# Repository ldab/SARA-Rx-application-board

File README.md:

# SARA-Rx application board

 SARA-R4 NB-IoT + Cat-M1 + GNSS application board - NINA-B3 with Secure MQTT

# **:heavy_exclamation_mark:BEFORE YOU DO ANYTHING, CHECK BATTERY POLARITY:heavy_exclamation_mark:**

## TODO

- [ ] More details about battery etc...
- [ ] !!! Better Socket close URC handler.
- [ ] Check AT response based on the last chars, in order to avoid missing URCs when after "OK" for example
- [ ] Implement Subscribe;

## Energy Budget

* 88mA active current;
* Code takes ~10 seconds to execute;
* Wakes every hour;
* 40uA Sleep current;
* 10 hours of light available;
* V charge ready = 3.67V;
* V Over discharge = 3.6V;
* V Over charge = 4.12V;

**Source Power Required = 3.8mW**

**Storage Required = 4.73mAh**

### Sleep Current

| Component 	| Current 	|
|-----------	|---------	|
| SARA-R410 	| 7uA     	|
| NINA-B3   	| 3uA     	|
| Batt ADC  	| 3uA     	|
| SHTC3     	| 0.5uA   	|
| TP4054    	| 1uA     	|
| TXS0108   	| 5uA(?)  	|
| TPS61021A  	| 17uA   	  |
| TOTAL     	| ~37uA   	|

## Nordic SDK

* This is based on nRF5_SDK_16.0.0_98a08e2, get yours here: https://www.nordicsemi.com/Software-and-tools/Software/nRF5-SDK/Download

1. Sign in to the AWS IoT Console
2. Register a Device in the Registry
3. Configure Your Device
4. View Device MQTT Messages with the AWS IoT MQTT Client

https://docs.aws.amazon.com/iot/latest/developerguide/iot-gs.html

* 120mA active current;
* Code takes 15 seconds to execute;
* Wakes every hour;
* 2mA Sleep current *This needs to be optimized*;
* 10 hours of light available;
* V charge ready = 3.67V;
* V Over discharge = 3.6V;
* V Over charge = 4.12V;

1. Clone this repo to a local folder ```> git clone https://github.com/ldab/SARA-Rx-application-board```
2. Point the `$(SDK)` @`./code/ninab3/blank/ses/libuarte_pca10056.emProject` to where you have installed Nordic SDK, for example `C:\nRF\nRF5_SDK_16.0.0_98a08e2`
3. Like so: `macros="CMSIS_CONFIG_TOOL=C:/nRF/nRF5_SDK_16.0.0_98a08e2/external_tools/cmsisconfig/CMSIS_Configuration_Wizard.jar;SDK=C:/nRF/nRF5_SDK_16.0.0_98a08e2"`
4. Open the SEGGER Embedded Studio project file located in `./code/ninab3/blank/ses/libuarte_pca10056.emProject`

* PS. don't forget to set the NFC Pins as GPIO on the Preprocessor: `CONFIG_NFCT_PINS_AS_GPIOS`

Ref. https://devzone.nordicsemi.com/f/nordic-q-a/44638/how-to-move-an-sdk-example-out-of-the-sdk-tree

## IoT Dashboard

* Adafruit https://io.adafruit.com provides a free MQTT broker with a Dashboard allowing this project to be displayed publicly with little to no effort
  * Create an account and insert your KEY as the `MQTT_PASS`
  * `MQTT_USER` is the username used for creating the account.

* Adafruit expect data as a json, for example:

    ```
    sprintf(_msg, "{\"feeds\": {\"T\": %.01f,\"H\": %.01f,\"Bpc\": %d,\"RSRP\": %.02f,\"Bv\": %.02f}}",
            temperature, humidity, batt_lvl_in_percentage, modemInfo.RSRP, _b)
    ```

* The topic, groups and feeds are created automagically, on the example the MAC address is added as an identifier:

    ```
    sprintf(topic, "lbispo/g/nina_%X/json", NRF_FICR->DEVICEADDR[0]);
    ```

https://io.adafruit.com/lbispo/dashboards/moree?kiosk=true

## Efficiency

## Schematic

## PCB

## BOM

## Enclosure

## Kown issues, limintations

* MQTT Socket Implementaition can only **publish** QoS 0 messages.

## Thoughts or Improvements

* Use STATUS 2 of AEM10941 as last grasp;
* Control boost converter EN, in order to turn SARA Off;
  * Remove boost converter, as it does not boost a lot since Vbatt ON = 3.6V.
* SARA RESET Pin access;
* Use 101b AEM10941 Configuration in order to Vovdis = 3.0V givin extra ~20% battery (?).
* Open Drain 74LVC3G07 buffer on NINA LED, in order to avoid leakage.

## Credits

* [MQTTBox](http://workswithweb.com/mqttbox.html) for Windows in order to communicate with the broker and check messages;
* [CloudMQTT](https://www.cloudmqtt.com/) Free Cloud Broker;
* MQTT implementation inspired and based on [knolleary PubSub Client](https://github.com/knolleary/pubsubclient);
* AT Commands implementation inspired on [vshymanskyy TinyGSM](https://github.com/vshymanskyy/TinyGSM);
* GitHub Shields and Badges created with [Shields.io](https://github.com/badges/shields/);

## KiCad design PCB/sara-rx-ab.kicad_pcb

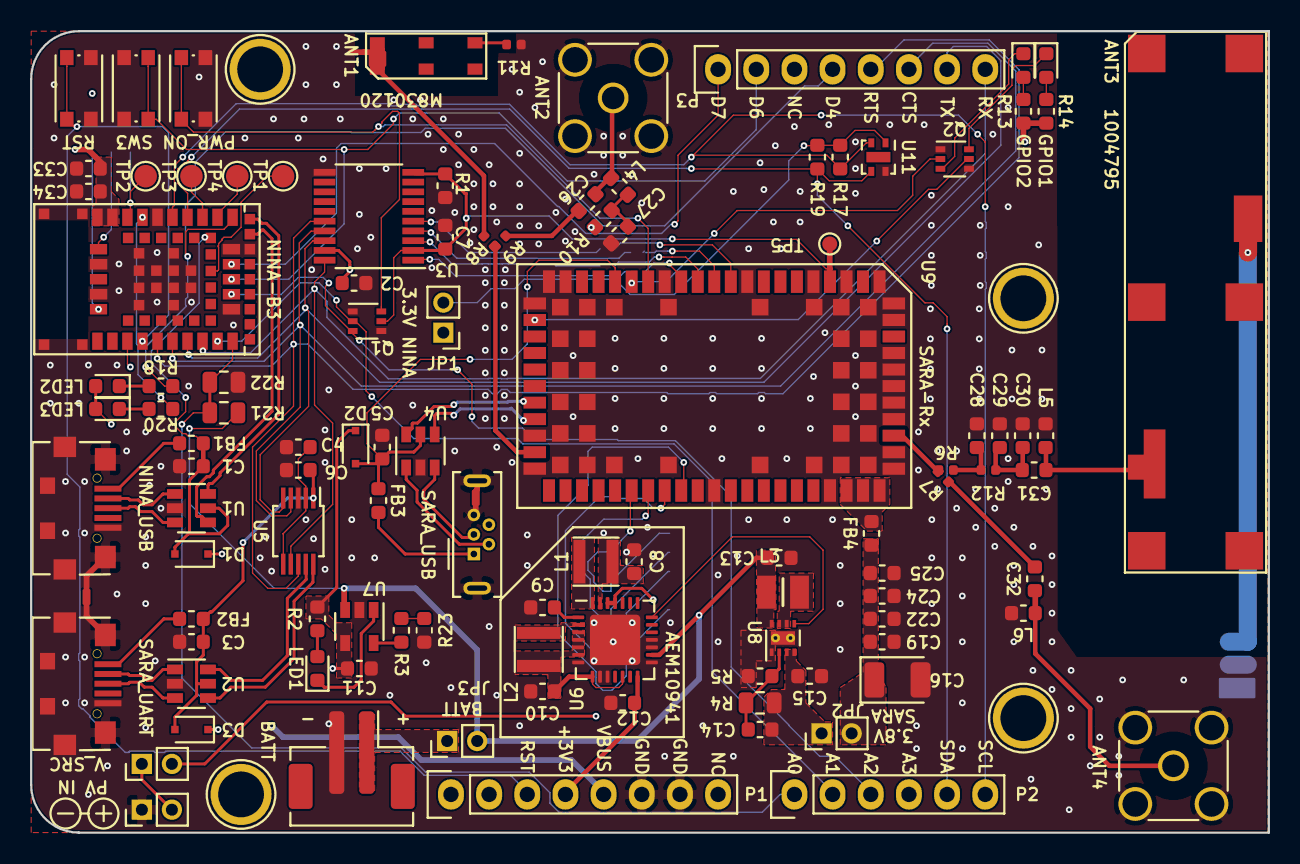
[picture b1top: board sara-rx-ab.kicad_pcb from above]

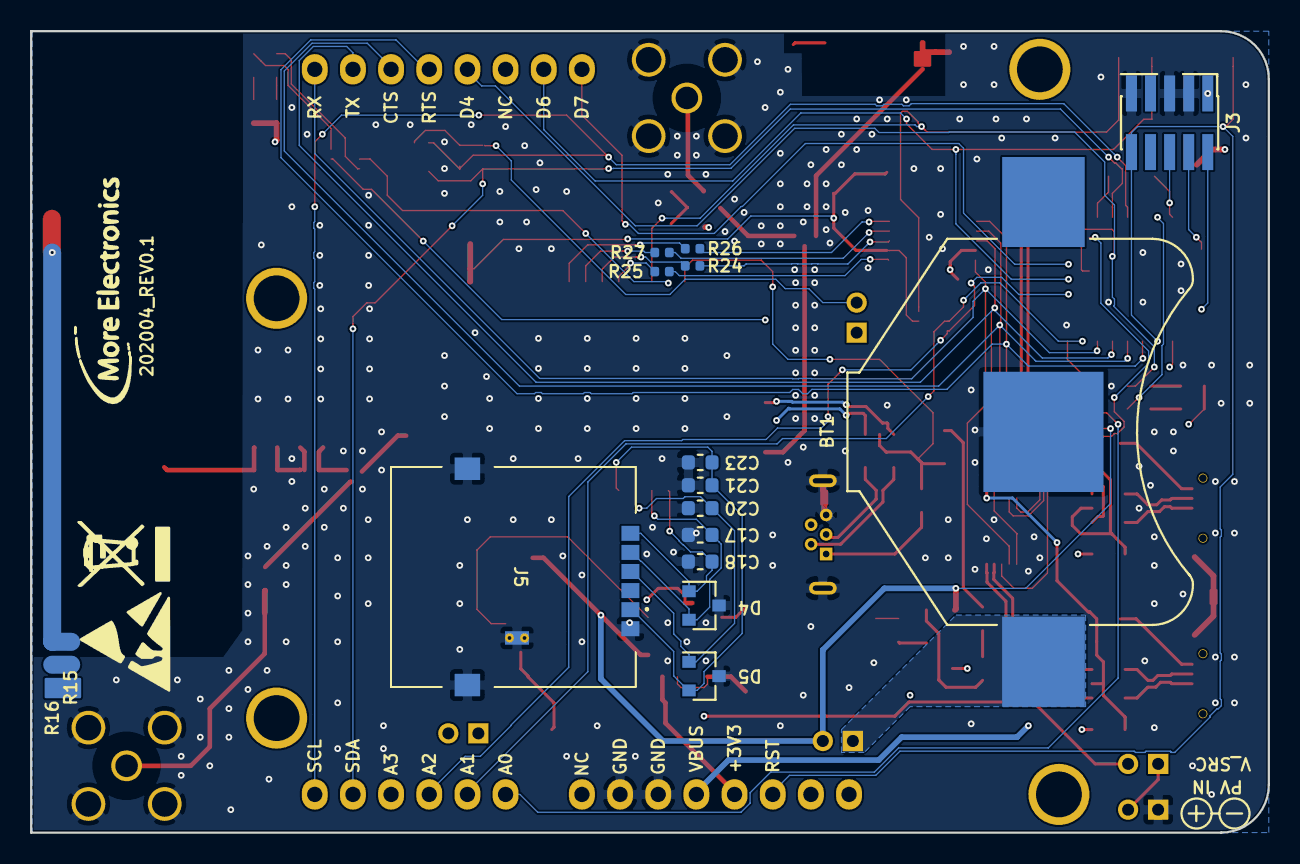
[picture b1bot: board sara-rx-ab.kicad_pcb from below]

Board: 4 copper layers, 82.4 x 53.3 mm, 128 parts (16 on the bottom side), 99 nets.

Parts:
ANT1: M830120
ANT2: Conn_Coaxial; SMA_Amphenol_132291_Vertical
ANT3: PCB ANT 1004795; 1009475
ANT4: EXT Antenna; SMA_Amphenol_132291_Vertical
BT1: LIR2450; BatteryHolder_Keystone_3008_1x2450
BT2: EXT BATT; JST_PH_B2B-PH-SM4-TB_1x02-1MP_P2.00mm_Vertical
C1, C2, C3, C5, C6, C7, C19, C23, C33, C34: 100n; C_0603_1608Metric
C4: 1u; C_0603_1608Metric
C8, C9, C10, C11, C12, C13, C15: 10u; C_0603_1608Metric
C14, C31: 4.7p; C_0603_1608Metric
C16: 100u; CP_EIA-3528-21_Kemet-B
C17, C18, C20, C21, C26: 47p; C_0603_1608Metric
C22, C27: 10n; C_0603_1608Metric
C24, C32: 15p; C_0603_1608Metric
C25: 68p; C_0603_1608Metric
C28: 5p; C_0603_1608Metric
C29: DNP; C_0603_1608Metric
C30: 0.3p; C_0603_1608Metric
D1, D2, D3: PMEG4010CEJ; D_SOD-323F
D4, D5: PESD5V0U2BT; SOT-23
FB1, FB2, FB3, FB4: BLM18EG221SN1D; L_0603_1608Metric
GPIO1, GPIO2: LTST-C191KGKT; LED_0603_1608Metric
J1: SOLAR PV; PinHeader_1x02_P2.00mm_Vertical
J2, J4: Bridge; 4Layer_15mil
J3: FTSH-105-01; SWD_JTAG
J5: SMO-1512; SMO1512
J6: Bridge; 4Layer_square
JP1, JP2, JP3, JP4: Jumper_NC_Small; PinHeader_1x02_P2.00mm_Vertical
L1, L2: 10u; L_Taiyo-Yuden_NRH30xx
L3: DFE252012P-R47M=P2; INDC2520X120N
L4: 27n; L_0603_1608Metric
L5: 8.2n; L_0603_1608Metric
L6: 39n; L_0603_1608Metric
LED1, LED2: 19-217/R6C-AL1M2VY/3T; LED_0603_1608Metric
LED3: LTST-C191KGKT; LED_0603_1608Metric
P1: Power; Socket_Strip_Arduino_1x08
P2: Analog; Socket_Strip_Arduino_1x06
P3: Digital; Socket_Strip_Arduino_1x08
P4, P5, P6, P7: CONN_01X01; Arduino_1pin
Q1, Q2: MUN5214DW1T1G; SOT-363_SC-70-6
R1, R2, R3, R17, R19, R23: 10K; R_0603_1608Metric
R4, R21, R22: 1M±0.1%; R_0805_2012Metric
R5: 267K; R_0603_1608Metric
R6, R8, R11, R12, R15, R16, R24, R25, R26, R27: 0R; R_0402_1005Metric
R7, R9: DNP; R_0402_1005Metric
R10: 10; R_0603_1608Metric
R13, R14, R18, R20: 1K; R_0603_1608Metric
SW1: PWR_ON; SW_Push_1P1T_NO_CK_KMR2
SW2, SW3: KMR2; SW_Push_1P1T_NO_CK_KMR2
TP1, TP2, TP3, TP4: TestPoint; TestPoint_Pad_D1.5mm
TP5: TestPoint; TestPoint_Pad_D1.0mm
U1, U2, U4: USBLC6-2SC6; SOT-23-6
U3: TXS0108EPW; TSSOP-20_4.4x6.5mm_P0.65mm
U5: HT42B534-MSOP; MSOP-10_3x3mm_P0.5mm
U6: AEM10941; QFN-28-1EP_5x5mm_P0.5mm_EP3.35x3.35mm
U7: TP4054; SOT-23-5
U8: TPS61021A; WSON-8-1EP_2x2mm_P0.5mm_EP0.9x1.6mm_ThermalVias
U9: SARA-Rx; ublox_SARA-G3_LGA-96
U10: NINA-B3
U11: SHTC3; AMS_QFN-4-1EP_2x2mm_P0.95mm_EP0.7x1.6mm
USB1: USB_B_Micro; C77238
USB2: USB_B_Micro_C77238; C77238
USB3: USB_B_Micro_C145795; USB_Micro-B_U-D-M5DD-W-1_VERTICAL

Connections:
+1V8: C7.1, Q1.5, R1.2, TP5.1, U3.2, U3.10, U9.4
+3V3: C2.1, C12.1, J3.1, JP1.1, P1.4, U3.19, U6.14
+3V3_NINA: C33.1, C34.1, JP1.2, LED2.2, LED3.2, R17.1, R19.1, U10.9, U10.10, U11.1
+3V8: C14.2, C15.2, JP2.1, R4.2, R10.2, R13.1, R14.1, U8.3, U8.4
+3V8_SARA: C16.1, C19.1, C22.1, C24.1, C25.1, FB4.1, JP2.2
+5C: C1.2, D1.2, FB1.1, U1.5, U10.31
+5F: C5.1, D2.2, FB3.1, U4.5, U9.17
+5P: C3.1, C6.2, D3.2, FB2.1, U2.5, U5.1
+BATT_SYS: C13.2, JP3.2, L3.1, R21.1, U6.16, U7.3, U8.8
+V_PV: JP4.2, U6.25, U6.26
/MCU_D+: U1.4, U10.54
/MCU_D-: U1.6, U10.55
/MCU_I_D+: U1.3, USB1.3
/MCU_I_D-: U1.1, USB1.2
/NINA-B3/LED_G: R20.2, U10.7
/NINA-B3/SWC: J3.4, U10.11
/NINA-B3/SWD: J3.2, U10.15
/POWER MGT/LDO_EN: U6.21, U8.5
/POWER MGT/VBATT: BT1.1, BT2.1, JP3.1
/POWER MGT/VBUCK: C10.1, L2.1, U6.3, U6.4, U6.5, U6.6, U6.8, U6.12
/POWER MGT/V_SRC: J1.2, JP4.1
/SARA-Rx/ANT_EXT: C32.2, R7.2
/SARA-Rx/ANT_INT: C28.2, R6.2, R12.1
/SARA-Rx/GNSS_EXT: C26.2, R9.2
/SARA-Rx/GNSS_INT: ANT1.6, J6.1, R8.2
/SARA-Rx/GPIO1: Q2.2, U9.16
/SARA-Rx/GPIO2: Q2.5, U9.23
/SARA-Rx/PWR_ON: Q1.6, SW1.1, U9.15
/SARA-Rx/SARA_CTS: R27.1, U3.4
/SARA-Rx/SARA_RTS: R26.1, U3.5
/SARA-Rx/SARA_RX: R25.1, U3.1
/SARA-Rx/SARA_TX: R24.1, U3.3
/SARA-Rx/SIM_CLK: C18.1, D4.1, J5.C3, U9.38
/SARA-Rx/SIM_IO: C17.1, D4.2, J5.C7, U9.39
/SARA-Rx/SIM_RST: C20.1, D5.1, J5.C2, U9.40
/SARA-Rx/VSIM: C21.1, C23.1, D5.2, J5.C1, U9.41
/SARA_D+: U4.4, U9.29
/SARA_D-: U4.6, U9.28
/SARA_I_D+: U4.3, USB3.3
/SARA_I_D-: U4.1, USB3.2
/UART_D+: U2.4, U5.10
/UART_D-: U2.6, U5.9
/UART_I_D+: U2.3, USB2.3
/UART_I_D-: U2.1, USB2.2
A0\BATT: P2.1, R21.2, R22.1, U10.25
A1\SARA_ON: P2.2, Q1.2, U10.24
A2\V_INT: P2.3, Q1.3, U10.27
A3: P2.4, U10.18
D4\LED_R: P3.4, R18.2, U10.1
D6\SW: P3.2, SW3.1, U10.28
D7: P3.1, U10.29
D10_CS: TP4.1, U10.2
D11_MOSI: TP3.1, U10.3
D12\MISO\SWO\LED_B: J3.6, TP2.1, U10.8
D13_SCK: TP1.1, U10.45
GND: ANT1.1, ANT2.2, ANT4.2, BT1.2, BT2.2, C1.1, C2.2, C3.2, C4.1, C5.2, C6.1, C7.2, C8.2, C9.1, C10.2, C11.2, C12.2, C13.1, C15.1, C16.2, C17.2, C18.2, C19.2, C20.2, C21.2, C22.2, C23.2, C24.2, C25.2, C27.1, C28.1, C29.2, C30.1, C33.2, C34.2, D4.3, D5.3, J1.1, J2.1, J2.2, J3.3, J3.5, J3.9, J4.1, J4.2, J5.C5, J5.MP1, J5.MP2, J6.2, L5.2, L6.2, P1.6, P1.7, Q1.1, Q1.4, Q2.1, Q2.4, R1.1, R5.1, R11.2, R22.2, R23.2, SW1.2, SW2.1, SW3.2, U1.2, U2.2, U3.11, U4.2, U5.3, U6.7, U6.9, U6.10, U6.15, U6.17, U6.18, U6.29, U7.2, U8.1, U8.9, U9.1, U9.3, U9.5, U9.9, U9.14, U9.20, U9.21, U9.22, U9.30, U9.32, U9.43, U9.50, U9.54, U9.55, U9.57, U9.58, U9.59, U9.60, U9.61, U9.63, U9.64, U9.65, U9.66, U9.67, U9.68, U9.69, U9.70, U9.71, U9.72, U9.73, U9.74, U9.75, U9.76, U9.77, U9.78, U9.79, U9.80, U9.81, U9.82, U9.83, U9.84, U9.85, U9.86, U9.87, U9.88, U9.89, U9.90, U9.91, U9.92, U9.93, U9.94, U9.95, U9.96, U10.6, U10.12, U10.14, U10.26, U10.30, U10.53, U10.56, U10.57, U10.58, U10.59, U10.60, U10.61, U10.62, U10.63, U10.64, U10.65, U10.66, U10.67, U10.68, U10.69, U10.70, U10.71, U11.4, USB1.5, USB1.6, USB1.7, USB1.8, USB1.9, USB1.10, USB2.5, USB2.6, USB2.7, USB2.8, USB2.9, USB2.10, USB3.5, USB3.6, USB3.7
MCU_CTS: P3.6, U3.17, U5.4, U10.21
MCU_RTS: P3.5, U3.16, U5.8, U10.20
MCU_RX: P3.8, U3.20, U5.7, U10.23
MCU_TX: P3.7, U3.18, U5.5, U10.22
NINA_RST: J3.10, P1.3, SW2.2, U10.19
unnamed: ANT1.3, R11.1
unnamed: ANT2.1, C26.1, L4.1
unnamed: ANT3.1, C31.1, L5.1
unnamed: ANT3.5, R15.1
unnamed: ANT4.1, C32.1, L6.1
unnamed: C4.2, U5.2, U5.6
unnamed: C8.1, L1.1, U6.27
unnamed: C9.2, U6.1
unnamed: C14.1, R4.1, R5.2, U8.2
unnamed: C27.2, L4.2, R10.1
unnamed: C29.1, C30.2, C31.2, R12.2
unnamed: FB1.2, USB1.1
unnamed: FB2.2, USB2.1
unnamed: FB3.2, USB3.1
unnamed: FB4.2, U9.51, U9.52, U9.53
unnamed: GPIO1.1, Q2.6
unnamed: GPIO1.2, R14.2
unnamed: GPIO2.1, Q2.3
unnamed: GPIO2.2, R13.2
unnamed: L1.2, U6.28
unnamed: L2.2, U6.2
unnamed: L3.2, U8.6, U8.7
unnamed: LED1.1, U7.1
unnamed: LED1.2, R2.2
unnamed: LED2.1, R18.1
unnamed: LED3.1, R20.1
unnamed: R3.1, U7.5
unnamed: R6.1, R7.1, U9.56
unnamed: R8.1, R9.1, U9.31
unnamed: R15.2, R16.1
unnamed: R3.2, R23.1
unnamed: R24.2, U9.12
unnamed: R25.2, U9.13
unnamed: R26.2, U9.10
unnamed: R27.2, U9.11
SCL: P2.6, R17.2, U10.5, U11.2
SDA: P2.5, R19.2, U10.4, U11.3
VBUS: C11.1, D1.1, D2.1, D3.1, P1.5, R2.1, U7.4

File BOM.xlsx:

| Quantity | Manufacture Part Number | Manufacturer(optional) | Description(optional) | LCSC Part Number(optional) | Package(optional)
ANT2 | 1 |  |  | Conn_Coaxial | C411575 | Connector_Coaxial:SMA_Amphenol_132291_Vertical
BT1 | 1 |  |  | LIR2450 | C238100 | Battery:BatteryHolder_Keystone_3008_1x2450
BT2 | 1 | B2B-PH-SM4-TB(LF)(SN) |  | EXT BATT | C160352 | Connector_JST:JST_PH_B2B-PH-SM4-TB_1x02-1MP_P2.00mm_Vertical
> C1-C3, C5-C7, C19, C23, C33, C34 | 10 | C1608X7R1E104KT000N |  | 100n | C338036 | Capacitor_SMD:C_0603_1608Metric
C4 | 1 | EMK107B7105KA-T |  | 1u | C92759 | Capacitor_SMD:C_0603_1608Metric
> C8-C13, C15 | 7 | JMK107BJ106MA-T |  | 10u | C87152 | Capacitor_SMD:C_0603_1608Metric
> C14, C31 | 2 | CC0603CRNPO9BN4R7 |  | 4.7p | C282071 | Capacitor_SMD:C_0603_1608Metric
C16 | 1 |  |  | 100u | C16133 | Capacitor_Tantalum_SMD:CP_EIA-3528-21_Kemet-B
> C17, C18, C20, C21, C26 | 5 | CC0603JRNPO9BN470 |  | 47p | C1671 | Capacitor_SMD:C_0603_1608Metric | replaced
C25 | 1 | GRM1885C2A680JA01D |  | 68p | C162261 | Capacitor_SMD:C_0603_1608Metric
> C22, C27 | 2 | CC0603KRX7R0BB103 |  | 10n | C107059 | Capacitor_SMD:C_0603_1608Metric
C28 | 1 | GRM1885C1H5R0BA01D |  | 5p | C162236 | Capacitor_SMD:C_0603_1608Metric
C30 | 1 | CL10C0R3CB8NNNC |  | 0.3p | C170140 | Capacitor_SMD:C_0603_1608Metric
> C24, C32 | 2 | CGA3E2C0G1H150JT0Y0N |  | 15p | C342889 | Capacitor_SMD:C_0603_1608Metric
> D1-D3 | 3 | PMEG4010CEJ |  | PMEG4010CEJ | C50704 | Diode_SMD:D_SOD-323F
> D4, D5 | 2 | PESD5V0U2BT |  | PESD5V0U2BT | C85399 | Package_TO_SOT_SMD:SOT-23
> FB1-FB4 | 4 | BLM18EG221SN1D |  | BLM18EG221SN1D | C17305 | Inductor_SMD:L_0603_1608Metric | replaced
J3 | 1 | 20021221-00010C4LF |  | FTSH-105-01 | C180221 | custom:SWD_JTAG
J5 | 1 | SMO-1512 |  | SMO-1512 | C125621 | SMO1512
 | 4 | C5664 |  | Jumper Shunt | C5664
> JP1-JP4 | 4 | MTP220-1102S1 |  | Jumper_NC_Small | C376075 | Connector_PinHeader_2.00mm:PinHeader_1x02_P2.00mm_Vertical
> L1, L2 | 2 | NRH3010T100MNV |  | 10u | C223113 | SamacSys_Parts:L_Taiyo-Yuden_NRH30xx
L3 | 1 | DFE252012P-R47M=P2 |  | DFE252012P-R47M=P2 | C237552 | INDC2520X120N
L4 | 1 | HK160827NJ-T |  | 27n | C222672 | Inductor_SMD:L_0603_1608Metric
L5 | 1 | VHF160808H8N2ST |  | 8.2n | C139273 | Inductor_SMD:L_0603_1608Metric
L6 | 1 | LQG18HN39NJ00D |  | 39n | C86134 | Inductor_SMD:L_0603_1608Metric | replaced
> LED1, LED2 | 2 | 19-217/R6C-AL1M2VY/3T |  | 19-217/R6C-AL1M2VY/3T | C72044 | LED_SMD:LED_0603_1608Metric
LED3 | 3 | LTST-C191KGKT |  | LTST-C191KGKT | C125098 | LED_SMD:LED_0603_1608Metric
> Q1, Q2 | 2 | MUN5214DW1T1G |  | MUN5214DW1T1G | C94403 | Package_TO_SOT_SMD:SOT-363_SC-70-6
> R1, R2, R17, R19,R3,R23 | 6 | 0603WAJ0103T5E |  | 10K | C15401 | Resistor_SMD:R_0603_1608Metric
> R4, R21, R22 | 3 | WF08H1004BTL |  | 1M±0.1% | C384461 | Resistor_SMD:R_0805_2012Metric
R5 | 1 | RC0603FR-07267KL |  | 267K | C185347 | Resistor_SMD:R_0603_1608Metric
R10 | 1 | 0603WAJ0100T5E |  | 10 | C25202 | Resistor_SMD:R_0603_1608Metric
> R6, R8, R11, R12, R15, R16 | 6 | 0402WGF0000TCE |  | 0R | C17168 | Resistor_SMD:R_0402_1005Metric
> R13, R14, R18, R20 | 4 | 0603WAJ0102T5E |  | 1K | C25585 | Resistor_SMD:R_0603_1608Metric
SW1 | 3 | K2-1809SN-D4DW-06 |  | PWR_ON | C128941 | SamacSys_Parts:SW_Push_1P1T_NO_CK_KMR2
U3 | 1 | TXS0108EPWR |  | TXS0108EPWR | C17206 | Package_SO:SSOP-20_4.4x6.5mm_P0.65mm
> U1, U2, U4 | 3 | USBLC6-2SC6 |  | USBLC6-2SC6 | C7519 | Package_TO_SOT_SMD:SOT-23-6
U5 | 1 | HT42B534 |  | HT42B534-MSOP | C95344 | Package_SO:MSOP-10_3x3mm_P0.5mm
U7 | 1 | TP4054 |  | TP4054 | C32574 | Package_TO_SOT_SMD:SOT-23-5
U8 | 1 | TPS61021A |  | TPS61021A | C193037 | Package_SON:WSON-8-1EP_2x2mm_P0.5mm_EP0.9x1.6mm_ThermalVias
U11 | 1 | SHTC3 |  | Temperature & Humidity Sensors | C194656 | Package_DFN_QFN:AMS_QFN-4-1EP_2x2mm_P0.95mm_EP0.7x1.6mm
USB1, USB2 | 2 | U-F-M5SS-W-1 |  | USB_B_Micro | C77238 | SamacSys_Parts:C77238
USB3 | 1 | U-D-M5DD-W-1 |  | USB_B_Micro_C145795 | C145795 | custom:USB_Micro-B_U-D-M5DD-W-1_VERTICAL

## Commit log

2019-12-06 fix timestamp and millis
2019-12-08 write/read socket implementation
2019-12-08 fix buffer size variable
2019-12-10 dev checkpoint
2019-12-16 mqtt_not_tested
2019-12-17 mqtt publish + SSL
2020-01-22 PCB rel
2020-04-08 i2c and SHTC3 Implementation
2020-04-08 test LEDs and Button
2020-04-09 update board dependancy
2020-04-22 PCB Rev0.1.0 Fix level shifter and silk
2020-05-04 UARTE low current
2020-05-07 All on RTC1 and Low Clock (sdk.config)
2020-05-11 DMA FIX and RTC
2020-05-11 Dev merge (#1)
    * dev checkpoint
    * mqtt_not_tested
    * mqtt publish + SSL
    * mqtt publish + SSL
    * PCB rel
    * i2c and SHTC3 Implementation
2020-05-17 initial release
2020-05-20 update README with dashboard
2020-07-01 beta release
2020-11-04 new current readings
2020-11-04 sleep current
2020-11-11 epishine power prof

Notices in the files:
README.md:
License: MIT
